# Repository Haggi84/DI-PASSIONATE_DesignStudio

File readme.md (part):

# Package Studio — chip packaging assemblies in FreeCAD, ready to simulate

Build an assembly — chips from GDSII, housings, lids, boards, as many of
each as the design has (a mixed-signal module with an RF chip and a
digital chip, two packages on one board) — wire it, define its ports and
materials, and get a **ready-to-run EM simulation package** for openEMS,
EMerge or Palace, written by OTTER. An assistant on a local model (Ollama)
explains the setup and changes it in plain words.

One toolbar, in the order the work goes:

| Button | What it does |
|---|---|
| **Technology** | Choose the PDK chips are imported with: IHP SG13G2, SkyWater SKY130, or your own folder |
| **Import GDS chips** | One or several layouts at once. Each comes in beside the others, with every drawn layer at its stackup height, its die body, oxide, passivation, bond pads and the PDK's materials. A layout that belongs to another technology is caught |
| **Housing library** | MirrorSemi open-cavity packages, JEDEC outlines, or your own STEP files. Each housing is its own package; its bond fingers become pads; a chip can go straight onto its paddle; a lid can be added |
| **Element Forge** | New housings from a sentence or a pasted datasheet table — a local model (Ollama) fills in the numbers, you check and edit them (values it assumed are marked), live 3-D preview, saved to your own library. Select a housing to change it in place: its pads keep their pin numbers, wires stay on their pins |
| **Import STEP part** | A board (a KiCad board exported as STEP, say), a lid, or a housing as it is |
| **Place** | A chip onto a die paddle or any face (a cavity floor, a board's copper), a lid onto a housing, a package onto a board's footprint — centred. What is placed then *belongs to* what it stands on and moves with it |
| **Move** | Move placed chips, lids, packages or boards — one or several at once — by typed offsets, arrow steps or dragging in the view. Offsets stay editable; wires follow |
| **Pads** | Chip pads from the layout; package pads from the bond fingers (one click finds them all); contact points on any flat surface |
| **Ports** | Simulation ports: rectangles in a face's plane, or standing on an edge up or down to the next edge |
| **Bond wires** | Material, diameter, wedge–wedge or ball–stitch; every bond dimension next to its MIL-STD-883 range; symmetric pairing, chip by chip; rule check |
| **Materials** | What every element is made of — thermal and electrical. The same values go into the EM simulation |
| **EM simulation** | Readiness check, exact chip metal, OTTER's checks, and the package — in one go with *Make simulation package* |
| **EM assistant** | Ask about the setup and have it changed: Ollama on this computer, or Claude / Gemini with your own key |

The menu also has **Layers** (show or hide every layer and part) and
**Export geometry** (STEP, OBJ, MSH for thermal or mechanical work).

## Installing

The workbench is a folder in FreeCAD's user Mod directory:

```
%APPDATA%\FreeCAD\v1-1\Mod\PackageStudio
```

Restart FreeCAD and choose **Package Studio** in the workbench selector. It
needs FreeCAD 1.0 or newer and `gdstk` in FreeCAD's Python
(`"C:\Program Files\FreeCAD 1.1\bin\python.exe" -m pip install gdstk`).
OTTER ships with it (`thirdparty/otter`); the solvers themselves (openEMS,
EMerge, Palace) run where you run the package. For the assistant, install
[Ollama](https://ollama.com) and pull a model (`ollama pull qwen3:8b`).

**For large chips, switch on OpenGL vertex buffers**: Edit › Preferences ›
Display › 3D View › *Use OpenGL VBO*. Turning a 2.3-million-triangle chip then
takes 37 ms a frame instead of 505 ms.

It can be installed beside Package Designer and DI-PASSIONATE: its code is
all in the package `pkgstudio`, its commands are `PS_…`, its settings under
`Mod/PackageStudio`.

## An assembly, step by step

A mixed-signal example: an RF chip and a digital chip, each in its own QFN,
both on one board.

1. **Technology** — pick the PDK. It is remembered.
2. **Import GDS chips** — select both GDS files at once. They come in side
   by side, 0.5 mm apart; each is checked against the technology on its own.
3. **Housing library** — pick a QFN, tick *Put the chip on the die paddle*.
   It takes the first chip not in a housing yet. Do it again for the second:
   the second housing is a second package, set 2 mm beside the first.
4. **Bond wires** — *Pair all, symmetric* pairs each chip with the leads of
   its own package, round its own centre; *Build wires*.
5. **Import STEP part › Board**, then **Place › Package onto a board** for
   each package: select the footprint's pads. The package becomes part of
   the board.
6. **Move** — nudge a package or a chip into its final place; the offsets
   stay editable.
7. **Ports** — draw the ports where the signals go in.
8. **Materials** — check what everything is made of.
9. **EM simulation › Make simulation package** — or fix what its list says
   first.

**Open and look:** `examples/lna_board/lna_rf_em.FCStd` is a finished EM
model — the IHP ALL_LNA in a QFN-24 on its RO4350B board, ports, materials
and EM settings set. Open it after cloning; the EM panel shows how it is
set up. See `examples/lna_board/README.md`.

The same steps as a script, ready to simulate: `examples/lna_qfn40_on_board.py`
(the SG13G2 LNA in a QFN-40 on its RO4350B test board, see `examples/README.md`).

## Element Forge: new housings in seconds

The model never writes geometry: it fills in a fixed set of numbers
(`core/elements.py`, the datasheet symbols D, E, A, e, b, L, D2, E2, A1 and
the lead counts), constrained to that schema by Ollama's structured output.
Every spec — typed, generated or loaded — goes through the same checks:
leads that would overlap, leads too wide for their pitch, too many leads for
the body, no lead length left, a name that disagrees with the numbers. A
spec that fails is handed back to the model once or twice with the exact
numbers; whatever is still wrong is listed with a fix to apply. Then the real
build is analysed like any housing: every lead must be bondable, the paddle
open.

- **Generate**: `QFN-24 4x4 mm, 0.5 mm pitch, exposed pad 2.6 mm`, or a
  datasheet's dimension table pasted in. The fields fill in as the model
  writes them.
- **Change**: `pitch 0.4, two more leads per side` — the element in the form
  is changed, the rest kept.
- Values the model **assumed** are amber (≈) until you change or confirm
  them.
- **Save to library** writes `<FreeCAD user data>/PackageStudio/elements/<name>.json`
  (or `$PKGSTUDIO_ELEMENTS`) — plain JSON, diff- and git-friendly. The
  Housing library lists them under *Mine*.
- Every housing built from numbers (JEDEC or Forge) keeps them
  (`ElementSpec`). **Update housing** rebuilds it in place.

## The design flow: pin list, LVS, assembly house, KiCad, circuit, measurement

The third toolbar, **Design flow**, connects the package to the people
around it (plan and rationale: `docs/plan/`):

| Command | For whom | What it does |
|---|---|---|
| **Pin list & LVS** | chip designer | Reads what the designer intends — CSV (`die,pad,net,kind,lead`), the xschem top cell (`.sch`), the digital flow's LEF — lays the wires **by net** (fixed leads kept as anchors, the rest crossing-free; for 2–3 dies an exact search over the lead arcs) and checks the package against it: opens, shorts, wrong leads, supplies without a lead, bonded `nc` pads, RF leads without ground neighbours |
| **Bonding diagram** | assembly house | SVG/PDF to scale and the wire list (CSV: first bond in µm from the die centre, second bond from the package centre, material, diameter, loop height, length) |
| **KiCad board** | board designer | Reads a `.kicad_pcb` (KiCad 6–9): its stack-up, lines, vias, planes, copper polygons, footprints — the whole board or a region for the EM model; packages go onto its footprints' lands |
| **KiCad library** | board designer | The package as a KiCad footprint (lands numbered as the leads — same numbering and positions as KiCad's own QFN library), a symbol whose pins carry the LVS nets, and a STEP model with dies and wires |
| **Circuit model** | chip designer | Touchstone → passive SPICE subcircuit (vector fitting, scikit-rf) + xschem symbol; with ngspice on the PATH it is simulated and compared with the Touchstone file |
| **Compare with measurement** | everyone who must trust the result | IEEE P370 quality of the measured data, 2x-thru de-embedding, max/RMS Δ per S-parameter, plot and report (`tools/ps_validate.py` does the same from the shell) |

Optional Python packages for the flow: `scikit-rf` (circuit model,
validation), `matplotlib` (plots); `ngspice` on the PATH for the circuit
model's check.

## Multi-chip modules, boards, systems

The second toolbar, **MCM & System**, takes an assembly beyond one die in one
package:

| Command | What it does |
|---|---|
| **Arrange dies (MCM)** | Several dies on one paddle — in a row, a column or corner to corner, a gap apart — and checked: on the paddle (with a margin for the die-attach fillet), clear of each other (≥ 0.15 mm), clear of the bond fingers (`core/mcm.py`) |
| **Wire the MCM** | Bond wires for all dies at once, crossing-free: the leads are shared out among the dies (a weighted Voronoi split of the lead ring), then each die is paired round its own centre. Die-to-die wires are ordinary wires between two chip pads; MIL-STD-883 judges their second bond as on a die pad (3.2.1.4a) |
| **PC/104 board** | A generated CubeSat board, 90.17 × 95.89 × 1.6 mm, 0.254 mm RO4350B over a ground plane on FR-4, corner holes, CubeSat Kit bus headers. From a script, `core/pcb.py` draws QFN land patterns, GCPW with via fences, traces, connectors and component bodies |
| **CubeSat 1U** | Rails, frames, M3 rods, spacers, solar panels, an S-band patch (`core/cubesat.py`) |
| **Into the system** | A board into the stack, at 15 mm pitch or a height you type; the spacers follow |
| **Integration check** | Envelope (100 × 100 × 113.5 mm, ≤ 6.5 mm out of a face, never on a rail), collisions between modules, every board's parts against the room in the stack, mass (≤ 2.00 kg) and centre of gravity (±2 cm) — CubeSat Design Specification Rev 14.1. Masses from the materials' densities |

The reference case is `examples/cubesat_sband_mcm.py`: an S-band receiver
front end from two real SG13G2 dies (the LNA and IHP's open
`i2c-gpio-expander`) in one QFN-32, on a CubeSat COM board, in a 1U CubeSat —
plus the RF path cut out of the board as an openEMS model. See
`examples/README.md`.

## Assemblies: what belongs to what

```
Assembly (the document)
  Board (App::Part)            imported STEP
    Package (App::Part)        placed on the board's footprint
      Housing, Lid             from the library, or STEP
      Chip (App::Part)         placed on the paddle
      Die attach, Bond wires
    Chip                       placed on the board's copper: chip-on-board
  Package 2 …
  Chip                         imported, not placed yet ("loose")
```

Chips come in **loose**, at the document's top level, beside one another.
**Place** puts a chip into the package of the housing it is placed on, or
into the board; a package placed on a board's footprint goes into the
board. From then on it moves with what it stands on, and its place is
kept exactly: only the container changes. A housing is always a package of
its own — a new one goes into the first package without a housing, else
into a new package beside the others.

**Bond wires** belong to the package or board both their pads are in, and
move with it. *Pair all, symmetric* pairs each chip on its own, with the
leads of its own package (or board), so two chips never take each other's
leads.

## Place and Move

**Place** is exact: the object's bottom centre onto the centre of the
selected face (or of several faces, such as a footprint's pads), its +Z
along their normal, turned in quarter steps. *Chip onto a die paddle* needs
nothing selected.

**Move** then moves it from there, *parametrically*: the place Place put it
is kept as its base, and a move is an offset from that base, kept in the
object's *Position* properties:

| Property | Meaning |
|---|---|
| OffsetX, OffsetY | moved along the surface it stands on, mm |
| OffsetAngle | turned about the surface normal, through its own bottom centre |

The X and Y of a move are its container's X and Y laid into the surface —
on a level paddle or board, the package's or board's X and Y, whichever way
the chip itself was turned — so several chips moved together all go the
same way. A turn is about each object's own centre.

In the **Move** panel:

- **select the rows** to move (Ctrl / Shift for several), or select them in
  the view and press *Take 3-D selection* — any face of a chip selects the
  chip;
- **step** them with the arrows (*Step*, default 0.05 mm) and turn them by
  the *Turn step*;
- **type** an offset in the table, or *Move by* ΔX ΔY;
- **drag**: *Drag in the view…*, click to grab, move — everything selected
  follows over its surface, snapped to the step — and click to drop. Esc
  puts everything back. Before grabbing, the arrow keys step and R turns;
- *Back to where placed* sets the offsets to zero; *Keep here as placed*
  makes the current place the new base.

Offsets typed in the property editor move the object too. Moved by other
means (FreeCAD's Transform), the next offset keeps that move. Wires are
rebuilt after every move — during a drag they are hidden and rebuilt on
the drop. Chips that overlap are reported.

## Technologies and the stack

A technology is a folder in `technologies/`: the PDK's KLayout layer
properties (`.lyp` — names and colours), its stackup (`.xml`) and a
`tech.json`. **Every height comes from the stackup XML** — the `.lyp` has
none, and a `.map` file (GDS ↔ LEF/DEF names) neither. Both stackup formats
in use are read and give the same heights:

- schema 2.0 (the bundled files): absolute `Zmin`/`Zmax` per layer and a
  `Substrate Offset`;
- schema 3.0 / 3.1 (IHP's current files, e.g. `SG13G2_FEM_200um.xml` from
  gds2palace): a layer or dielectric placed on another's `Top`/`Bottom`
  edge (`Reference`/`ReferenceEdge`), and `<Variables>` with `=expression`
  values (arithmetic only; nothing else is evaluated).

z = 0 is the top of the silicon. Checked against the PDKs (µm):

| SG13G2 | z | SKY130 | z |
|---|---|---|---|
| Metal1 | 1.04 – 1.46 | li1 | 0.9361 – 1.0361 |
| Metal5 | 5.09 – 5.58 | met1 | 1.3761 – 1.7361 |
| MIM | 5.6043 – 5.754 | met3 | 2.7861 – 3.6311 |
| TopMetal1 | 6.4303 – 8.4303 | met5 | 5.3711 – 6.6311 |
| TopMetal2 | 11.2303 – 14.2303 | | |
| SiO2 / passivation | 0 – 15.7303 / – 16.1303 | SiO2 | 0 – 6.6311 |
| EPI / substrate | −3.75 – 0 / 180 µm | EPI / substrate | −2 – 0 / 298 µm |

On import the chip gets, besides its drawn layers and its silicon:

- **the oxide and passivation**, die-sized, hidden and not pickable (shown,
  they would cover every pad) — offered in the export, not ticked, since
  they enclose the metal;
- **the unused PDK levels** — stack levels the PDK has and this layout does
  not draw (a digital chip without MIM, say), as faint die-sized slabs at
  their true height, listed in **Layers** under *Unused PDK levels*. They
  are not metal and are not ticked in the export.

**The wrong technology** builds nothing: no layer matches, and the chip
comes in as a bare block (an IHP layout imported as SKY130 does exactly
that). Import GDS counts how many of the layout's layers each technology
knows and offers the one that fits — ALL_LNA: SG13G2 knows 68 of 70, SKY130
one marker layer.

## Housings

| Source | What it is |
|---|---|
| **MirrorSemi** | MirrorSemi's pre-moulded open-cavity QFN/DFN packages (mirrorsemi.com), ready for die attach and wire bonding. *Load catalogue* reads their CAD page; a model is downloaded only when chosen, into a cache in your FreeCAD user folder. Nothing of theirs is shipped — their files are "all rights reserved", for your own use. A link that leads nowhere is reported, not imported. |
| **JEDEC** | Open-cavity packages generated from JEDEC outlines: QFN (MO-220), DFN (MO-229), LQFP/TQFP (MS-026), SOIC (MS-012), TSSOP (MO-153). Leadframe (paddle and leads, gull-wing outside where the outline has them) and a body with a cavity down to the bond fingers. |
| **Local folder** | Any folder of your own housing STEP files. |

Every housing, whatever its source, is read the same way: the solid with the
largest footprint is the body; the leadframe piece under its centre is the
die paddle; pieces reaching one side of the body are leads, pieces reaching
two are tie bars. A lead's *bond finger* is its top face where the body does
not cover it. This needs the leadframe as separate solids, as MirrorSemi's
models and the generated packages have it; a fully moulded body exposes no
fingers. Body and leadframe get mould compound and copper alloy C194; change
either in **Materials** (MirrorSemi bodies are pre-moulded — LCP is in the
library).

Lids are generated flat, the size of the body, in glass, ceramic, LCP or Kovar.

## Bond wires

Two bond types, shaped as a bonder makes them:

- **Wedge–wedge** (ultrasonic, aluminium — the default): a wedge on the chip
  pad and one on the lead; the wire leaves the first wedge's heel at the
  tool's wire-feed angle (45° by default), not vertically, and a short tail
  is left beyond the last wedge.
- **Ball–stitch** (thermosonic, gold, copper, silver): a flattened ball with
  the capillary's chamfer cone on the chip pad, the wire leaving it
  vertically, and a crescent stitch on the lead.

**The wire is one swept solid, wedges included.** Its centreline runs over
the first foot, bends out of the heel (radius 1.5 d), follows the loop,
bends into the second foot and runs on into the tail. The cross-section
along it is the round wire in the loop and the flattened bond on each foot,
changing over the bends, as the tool squashes the wire. There are no
separate bond blocks for the wire to sit on. A bond's thickness is not set
but follows from the wire: the flattened section keeps the wire's area
(1.5 d wide → 0.57 d thick). Each foot is sunk a tenth of its thickness into
its pad and cut flat, so **it meets the surface in a flat contact face lying
in the pad's plane** (31.8 × 70 µm for a 25 µm wire's first wedge). This
holds on a tilted surface too: each end follows its own pad's normal. The
loop's highest point is exactly the loop height.

### Wires onto a board: contact points

A board, substrate or any flat face without pads of its own gets
**contact points**: Pads › *Contact points*.

1. Select the face the wires land on and press **Use selected face**. The
   panel shows its size, e.g. *100.0000 x 50.0000 mm (X x Y)*.
2. Choose the **origin**: the *face corner* (default; X runs along the
   face's edge nearest the chip's x axis, Y across it, so a 100 x 50 mm
   face runs from (0, 0) to (100, 50)), or the *chip centre* (X, Y along the
   chip's axes).
3. A **grid with rulers** is drawn on the face in these coordinates:
   labelled lines about ten across the face in 1-2-5 steps (10 mm on a
   100 mm face), fine lines a fifth of that, millimetre labels along the X
   and Y edges. Set the spacing yourself in *Grid*, or switch it off. It is
   temporary: not exported, gone when the panel closes.
4. Type **X** and **Y** in mm and press **Add point**: X 25.5, Y 10 puts it
   exactly there. Or **Click points…** on the face (Esc ends): a red
   crosshair follows the mouse and the panel shows the X and Y a click
   would give, snapped to the fine grid lines (switch off *clicks snap*
   for free positions); a click off the face is refused.
5. The table lists every point's X and Y; edit a value to move the point.
   A point is the size of the bond that lands on it (62.5 x 37.5 µm for
   25 µm wire); *Point size › Apply* resizes the selected ones (or all).
6. Select points in the table and **Mirror** them over X (through the
   face's middle: Y → 50 − Y on a 100 x 50 face), over Y (X → 100 − X), or
   both. With the chip-centre origin the mirror lines are the chip's axes.
   An image already there, or off the face, is not made.
7. **Bond wires › Pair all, symmetric** (or *Pair selected pads*) and
   **Build wires**: their second wedges lie flat on the face.

### The rule check

The rule check applies MIL-STD-883, Test Method 2010 (internal visual),
class level B (Condition B, the default) or S (Condition A):

| Clause | Criterion |
|---|---|
| 3.2.1.1a | Ball diameter 2.0 – 5.0 × wire diameter |
| 3.2.1.1c | Ball: wire centre exit within the pad opening |
| 3.2.1.2a/b | Wedge 1.2 – 3.0 × wide (ultrasonic) or 1.5 – 3.0 × (thermosonic stitch), 1.5 – 6.0 × long |
| 3.2.1.4a | ≥ 75 % (S) / ≥ 50 % (B) of the bond on the die within the pad opening |
| 3.2.1.4d | Tail ≤ 2 wire diameters |
| 3.2.1.4e | Bond completely on the lead |
| 3.2.1.4f | Bond to bond: ≥ 0.25 mil (S) / a gap (B) |
| 3.2.2a | Wire to other wires, bonds, leads, the die edge, the lid: ≥ 2 d (S) / ≥ 1 d (B); class S accepts 1 mil within 5 mil of the bond on the die |
| 3.2.2d | No straight run without an arc |
| 3.2.2e | No wires crossing seen from above, except at different heights with ≥ 2 d |

Two assembly guidelines are reported as notes, not rejects: wire length
≤ 200 × diameter (5 mm for 25 µm) and a loop of at least 75 µm for ball
bonds (neck damage below that) or 2 × diameter for wedges. Each row of the
table shows ✓ or ✗; hovering lists every finding with its clause.

## Ports

**Ports** has its own command. A port is a flat rectangle where the
simulation feeds and measures the model.

**In a face's plane**: select a face (or an edge — the flat face beside it
that stands most upright is taken: a board's top-rim edge gives its edge
face), press **Use selected face**, choose the origin, and type the port's
centre and **Add port**, or **Click port centres…** with the grid and
crosshair. Give its size (W along the face's X, H along its Y), type
(*lumped* or *wave*), impedance (50 Ω) and, for a lumped port, the direction
of its field (±X or ±Y in its own plane). The table edits position, size,
type and impedance; **Mirror selected** mirrors over X, Y or both. Ports are
named Port1, Port2, … (P1 is often a chip pad's name).

**Or draw it on an edge.** **Draw on an edge…**, in the same box, needs no
face chosen first. It takes three clicks per port:

1. Click an edge of a chip layer, a board, a housing or a lid. The port
   starts there.
2. Click again along that edge to set the port's length.
3. Move the mouse up or down and click to set its height.

The port stands upright on the edge, and the next port can be drawn
straight away. **Esc** abandons the port being drawn; **Esc** again ends.
On a chip layer the edge is the side of the drawn GDS polygon nearest the
click, at the layer's top or bottom. The layer is shown as a mesh, and the
mesh's triangle edges are not the polygon's. Two choices set the numbers:

| Choice | Effect |
|---|---|
| **Length: from the two clicks** | The length is between the two clicks. |
| **Length: W above** | The length is W; the second click only says which way along the edge the port runs. |
| **Height: follow the mouse** | The height is where the cursor is. |
| **Height: H above** | The height is H; moving up or down picks the direction. |
| **Height: to the next edge above / below** | The port ends at the nearest edge of other shown geometry over or under its length. That is usually the ground under a trace, or for a chip layer the silicon's top. Moving up or down picks which. |

"Next edge" is measured exactly. B-rep parts (board, housing, lid, die body)
are cut with the port's own plane. A chip's layers are taken from their
GDS polygons: every polygon the port's footprint crosses gives its layer's
bottom and top. The body the port starts on doesn't count: from a trace's
top, the next edge below is the ground, not the trace's own underside.
Hidden layers and the faint slabs of levels the layout does not draw don't
count either. Show the oxide, and its boundaries count too. Type, Z0 and
field direction come from the box above. A port drawn on an edge is an
ordinary port afterwards: in the table, in the exports, and in
`ports.json`.

Ports are drawn as opaque faces, in front of the faces they lie in. A port
on an edge shares its plane with the side faces there, and when it was
drawn see-through the edges behind showed through, so it looked like an
outline.

Ports are drawn as opaque faces, in front of the faces they lie in.

**A lumped port spans the gap between two conductors**, the signal and its
ground: from a trace down to the ground plane, or in a QFN's leadframe
plane from a lead's inner end across to the die paddle. One that touches a
single conductor is warned about; one that touches none is an error — it
would feed nothing.

## Materials

Every element has a material with density, thermal conductivity, specific
heat, CTE, electrical conductivity, permittivity, permeability and loss
tangent. **There is one material system**: what the Materials panel says is
what the exports write and what the EM solver gets; a material changed in
the EM panel is written back to the element. They come from three places:

- **The chip's technology** — every material in the PDK stackup, with the
  PDK's own conductivity and permittivity (SG13G2 Metal1: 21.64 MS/m), and the
  thermal values of the bulk material it is made of.
- **The library** — bond-wire metals, leadframe alloys, moulding compounds,
  laminates, ceramics, glass; typical values with their sources.
- **Your own** — *New material…* in the Materials panel, kept in
  `PackageStudio/materials.json` in FreeCAD's user folder.

From 10⁴ S/m up a material is a conductor in the EM model (Ag-filled die
attach at 10⁵ S/m is one); below, a dielectric with its ε_r and tan δ (doped
silicon at 2 S/m is a lossy one). Set *not simulated* to leave an element
out.

## EM simulation

**EM simulation** opens a panel that goes from the assembly to a
ready-to-run package. **Make simulation package** does it all and stops at
the first thing that would make the result wrong, saying which command
fixes it. The steps, one by one:

**0. Ready to simulate?** — what the assembly still lacks, worst first:

| Error (stops) | Warning (a guess the result depends on) |
|---|---|
| no port, no excited port, two ports with one number | parts without a material — OTTER guesses from name and colour |
| a material not in the library, or without ε_r and σ | a chip not placed in a housing or on a board |
| a chip region too big to mesh | a port touching only one conductor |
| chips overlapping | MIL-STD-883 rejects on the wires |
| a wire that lost a pad; after the build: a port touching no conductor | |

**1. Chip metal** — a whole chip cannot be meshed for EM (ALL_LNA has
600,000 vias) and does not need to be: what the package adds is pad, wire
and lead. So each chip's metal is rebuilt **exactly from its GDS polygons**
inside a region — by default round the pads that have wires, 20 µm beyond
them — for the levels chosen (by default the two highest metals and the vias
between). **Fill is left out**; via arrays become blocks whose conductivity
is scaled by how much of them is via. The rest of the die is its silicon,
oxide and passivation. The table shows how many polygons each chip builds
(at most 60,000).

**2. Model** — a separate document, *<assembly> (EM model)*: every physical
part where it really is (housing, leadframe, die attach, lid, board, wires,
die body, oxide), the chip metal, one face per port, and an air box a
quarter wavelength round everything at the highest frequency (2.6 mm at
30 GHz). The assembly itself is not changed.

**3. Solver** — openEMS (FDTD), EMerge (FEM) or Palace (FEM); frequency
range; mesh density and smallest cell.

**4. Layers and materials** — the layer stack OTTER sees, each layer's
material and where it came from; guessed ones are marked. *Save chosen
materials to the assembly* writes a choice back to the elements.

**5. Ports** — every port as a lumped port with its impedance and its
excitation axis; which one is excited.

**6. Checks** — OTTER's own checks, and the openEMS mesh estimate.

**7. Package** — written by the OTTER add-on itself into a zip: the solver
script and the geometry it loads, the flat model (`.FCStd` + `.ini`, to open
with the OTTER add-on), `overview.svg`, `materials.json` (every layer, its
values and where they came from) and a README with the run command, the
chip regions, the mesh estimate and every remaining finding.

### Click a finding: the fix, shown in the 3-D view

Every line of *0. Ready?* and *6. Checks* can be clicked. A box under the
list explains it in the assembly's terms. The 3-D view zooms to it and
draws:

| Colour | Meaning |
|---|---|
| red | the part the finding is about |
| yellow | the conductors a fix would join |
| green | the fix itself |

Where the fix can be worked out, it is a button; applied, the model is
built and checked again. Otherwise *Open Ports / Materials / Move / Place*
opens the command that fixes it by hand. The preview is temporary: it goes
when another line is clicked, a fix is applied, or the panel closes.

| Finding | What is shown | The fix |
|---|---|---|
| a port with no conductor at one or both ends | the port; the nearest conductor below its centre and above it, in its footprint | the port stretched or shrunk exactly between the two; if only one side has a conductor, that end. With none in its footprint, the nearest conductors anywhere are shown, to move it to |
| a port touching only one conductor | as above | as above |
| wires in cells larger than the wire | the parts named (often via blocks OTTER reads as wires) | their own cells of at most their diameter / 1.5 — fine cells only there |
| too many mesh cells | the part that sets the model's extent | coarse mesh density; smallest cell 2 µm |
| a sub-micron cell | | smallest cell 1 µm |
| no or several excited ports | | excite the first port only |
| air boundary too close | | air box a quarter wavelength away |
| a part without a material, an unplaced or overlapping chip, a broken wire | the parts concerned, selected | *Open Materials / Place / Move / Bond wires* |

## EM assistant

The assistant panel is a chat about the EM setup. It can only do what the
panel can — solver, frequency, material per layer, mesh, ports, checks, and
search OTTER's documentation — through a fixed set of tools, each checked
like a click; it never sees or writes solver code. With every question it
is given the project, where each material came from, and the readiness
findings, so it can say what is missing and which command fixes it.

- **Local model (Ollama)** — the default: free, and nothing leaves the
  computer. The panel says whether Ollama answers at its URL
  (`http://127.0.0.1:11434`) and lists the models pulled.
- **Claude** or **Gemini** with your own API key: the project description
  and your questions go to that provider. A key is kept for the session,
  or in FreeCAD's `user.cfg` if you tick *remember*.

Build the model first (*Build model* or *Make simulation package*).

## Export geometry: what is written, exactly

Chip layers are rebuilt from the GDS polygons at export time — never from
what the view shows. Every polygon becomes a prism of its layer's height,
vertex for vertex. Metal fill is metal and is included; slits are cut out;
pin, label and boundary shapes are markers and are not.

| File | Content |
|---|---|
| STEP | Exact solids, one named product per element (`Chip/Metal1_8_0`, `Wires/Wire P1 - 1`, …) |
| OBJ | Triangle meshes, one named group per element, coloured by material. Chip layers are exact; curved parts follow the chosen deviation |
| MSH | Gmsh 4.1 volume mesh from the exact STEP: one physical group per element, and one per material (`MAT_…`) |
| `…_materials.json/.csv` | Each element, its material and every property, with units — written beside every export |

Exact solids cost about 0.6 ms per layout polygon; the export dialog says how
long before it starts, and can be cancelled.

**Only a section**: tick *Only a section* in the export dialog and press
**Pick in view…**: the view turns to the top; click two opposite corners —
a red rectangle follows the mouse — or type x and y from/to in mm. Only what
lies inside is written, at every height: chip layers are cut polygon by
polygon before any solid is built (so a section of a large chip is quick),
everything else is cut to the box. Elements wholly outside are left out, and
so are ports outside it from `_ports.json`.

## Limits

- Overlapping polygons on one layer are exported as overlapping prisms (only
  layers with slits are merged).
- Elements in an MSH geometry export are meshed independently (not conformal
  across touching elements).
- The EM model's passivation has no openings over the pads; the wire's foot
  takes their place.
- Housing analysis needs the leadframe as separate solids.
- Material values in the library are typical; for a production simulation,
  use your suppliers' datasheets (add them as your own materials).

## Tests

```powershell
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
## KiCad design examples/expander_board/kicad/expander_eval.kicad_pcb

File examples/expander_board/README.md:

# Expander evaluation board — chip, package, board, EM

The IHP i2c-gpio-expander (SG13G2, open MPW TO_Nov2024) from die to a
board that does something, back into FreeCAD, and on to an EM model.

## What the board does

It makes the expander usable from any 3.3 V I2C controller (Raspberry Pi,
microcontroller, Qwiic / STEMMA QT boards; daisy-chained over J1/J2):

| Block | Parts | Why |
|---|---|---|
| Supply | J1/J2 3.3 V → U2 AP2112K-1.2 → R2 0 Ω → U1 VDD (leads 2, 13) | the core takes 1.1–1.2 V; R2 lifted = an ammeter for the core current |
| Decoupling | C4/C5 100 nF at each VDD lead, C6 1 µF, C2/C3 1 µF at the LDO, C1 10 µF | |
| Clock | X1 50 MHz CMOS oscillator (Abracon ASE, 3.3 V) → R1 33 Ω at the source → lead 7 | the design is synchronous at 50 MHz from an external clock (IHP); the one fast net |
| Reset | R6 10 k / C8 100 nF (~1 ms), SW1, J4 | IHP: hold reset ≥ 1 µs while the core supply settles |
| I2C | R3/R4 2.2 kΩ (400 kHz fast mode), R5 10 k on INT | the pads are open drain, pull-ups needed (IHP) |
| Address | R7–R9 10 k pull-downs, JP1–JP3 to 3.3 V | default 0b000 |
| GPIO | J3 2x5 header (GPIO0–7, 3.3 V, GND), D1–D8 with 1 kΩ | |
| Test | TP1 CLK, TP2 +1V2, TP3 +3V3, TP4 GND | |

4 layers, 45 x 32 mm, 1.6 mm FR-4: F.Cu signals over In1 = GND, In2 = 3.3 V
(both layer type "power plane": no tracks on them), B.Cu, ground pours on
both outer layers. Every SMD pad of GND and 3.3 V reaches its plane through
a short track and a via (fan-out in `route_board.py`).

**Open point — read this first.** The die has no IOVDD/IOVSS pads (IHP's
`doc/source/known-issues.rst`): the IO ring has no supply pad of its own.
Whether the IOs work at all, and at which levels, is not known. The board
is built as the chip was meant to be used (3.3 V IO); it is also the test
fixture to find out — TP1–TP4, R2 for the core current, J4 for reset/INT.

The package: IHP packages its open tapeouts in QFN or open QFN with 24 to
64 pins, so a **QFN-24 4x4**, not a QFN-20: 20 wires, 4 leads unused.

## Files

| File | What |
|---|---|
| `expander_pinlist.csv` | the pin list with the board's net names (signal pads by GDS name, supply pads by their GDS labels) |
| `make_package.py` | step 1 (FreeCAD): die in QFN-24, wires by the pin list, LVS, MIL-STD-883, KiCad library, bonding diagram |
| `make_board.py` | step 2 (KiCad's Python): schematic, project, placed board |
| `route_board.py` | step 3 (KiCad's Python + Freerouting): routing, ground pours |
| `check_netlist.py` | the schematic's netlist against the design, ERC-like checks |
| `make_assembly.py` | step 4 (FreeCAD): the board back in, package on U1, the clock path cut out |
| `kicad/` | **the KiCad project** — open `expander_eval.kicad_pro` |
| `doc/` | schematic PDF, board picture, DRC report |

`kicad/` is written by KiCad 7 (schematic, board) and by Package Studio
(`ExpanderEval.*`, KiCad 8 format): open it with **KiCad 8 or 9**, which
converts the KiCad 7 files when you save.

## Checked

- Package: 20 wires, LVS 0 errors, MIL-STD-883 TM 2010 0 rejects, wires 1.42–1.80 mm.
- Schematic: its netlist (kicad-cli) equals the design — 29 nets, 128 pins;
  every power input driven, no two outputs on a net, no single-pin net.
  KiCad's own ERC was not run here (KiCad 7's kicad-cli has none): run it.
- Board: fully routed (0 unconnected); DRC 0 errors, 32 warnings (silkscreen
  overlaps — tidy the reference texts before ordering). KiCad's own ERC and
  DRC run in the KiCad GUI: 0 errors each (the one ERC warning is KiCad 7
  not reading the KiCad 8 library).
- FreeCAD: the board reads back with all 29 nets, the package lands with
  lead 1 on pad 1.

Found on the way and fixed in Package Studio:
- the exported QFN-24 4x4 footprint had touching corner lands (pads 6/7 =
  GPIO5/CLK shorted): `pcb.qfn_lands` keeps 0.2 mm between corner lands;
- KiCad zone fills with holes (one outline with slits) came in with the
  holes misread — the In1 ground under U1 was missing: `kicad_board._rings`;
- the EM panel built the model with OTTER's default 1 µm cells and ran out
  of memory on a board cut-out: it now takes the panel's mesh setting;
- the generated openEMS script's graded-mesh helper took > 7 GB for ~700
  mesh regions: Package Studio evaluates it in chunks (same lines, 0.45 GB).

## Steps

In FreeCAD (Package Studio):

1. *Import GDS* → `examples/data/i2c_gpio_expander_SG13G2Top.gds.gz`.
2. Housing from the JEDEC catalogue: **QFN-24 4x4**; *Place* the chip on the paddle.
3. *Pin list & LVS* → *Load pin list…* → `expander_pinlist.csv` → *Lay wires by net* → *Check (LVS)*.
4. *Bonding diagram* → a folder (for the assembly house).
5. *KiCad library* → a folder: footprint, symbol, STEP. (Already in `kicad/`.)

In KiCad 8/9:

6. Open `kicad/expander_eval.kicad_pro`. The project's library tables
   point at `ExpanderEval.*` in the project folder.
7. Schematic: *Inspect → Electrical Rules Checker*. Change what you need
   (another oscillator, other connectors), then *Tools → Update PCB from
   Schematic*.
8. Board: check, tidy the silkscreen, *Inspect → Design Rules Checker*,
   refill zones (B). Re-route if you moved things (interactive router, or
   Freerouting as in `route_board.py`).
9. Save.

Back in FreeCAD:

10. *KiCad board* → `expander_eval.kicad_pcb`, region empty → the whole
    board. Select the package and U1's lands → *Place*.
11. *KiCad board* again, region **`113, 110, 126.5, 125`** (KiCad mm): the
    clock path X1 → R1 → U1 with the ground around it. Place the package on U1.
12. *Ports* and 13. *EM simulation*: step by step, with screenshots, in the
    guide "Anleitung: Expander-Board in KiCad und Package Studio bis zur
    EM-Simulation" (a Claude doc). In short: four ports — X1's output and
    U1's leads 7 and 8 standing from the land down to In1, R1 as a 33-ohm
    lumped port that is not excited —; chip metal "No metal", 0.01–3 GHz,
    mesh coarse / 50 µm set before the build; *Make simulation package*:
    5.15 M cells, ~0.8 GB. `make_assembly.py` sets the same ports.

Scripted, the same:

    freecadcmd examples/expander_board/make_package.py
    python3   examples/expander_board/make_board.py         # KiCad's Python
    python3   examples/expander_board/route_board.py freerouting.jar
    freecadcmd examples/expander_board/make_assembly.py

`make_board.py` writes the board unrouted: run `route_board.py` after it.

Sources: IHP-GmbH/TO_Nov2024 `i2c-gpio-expander` (pin-out, design notes,
known issues; GPLv3), packaging options in that repository's README.

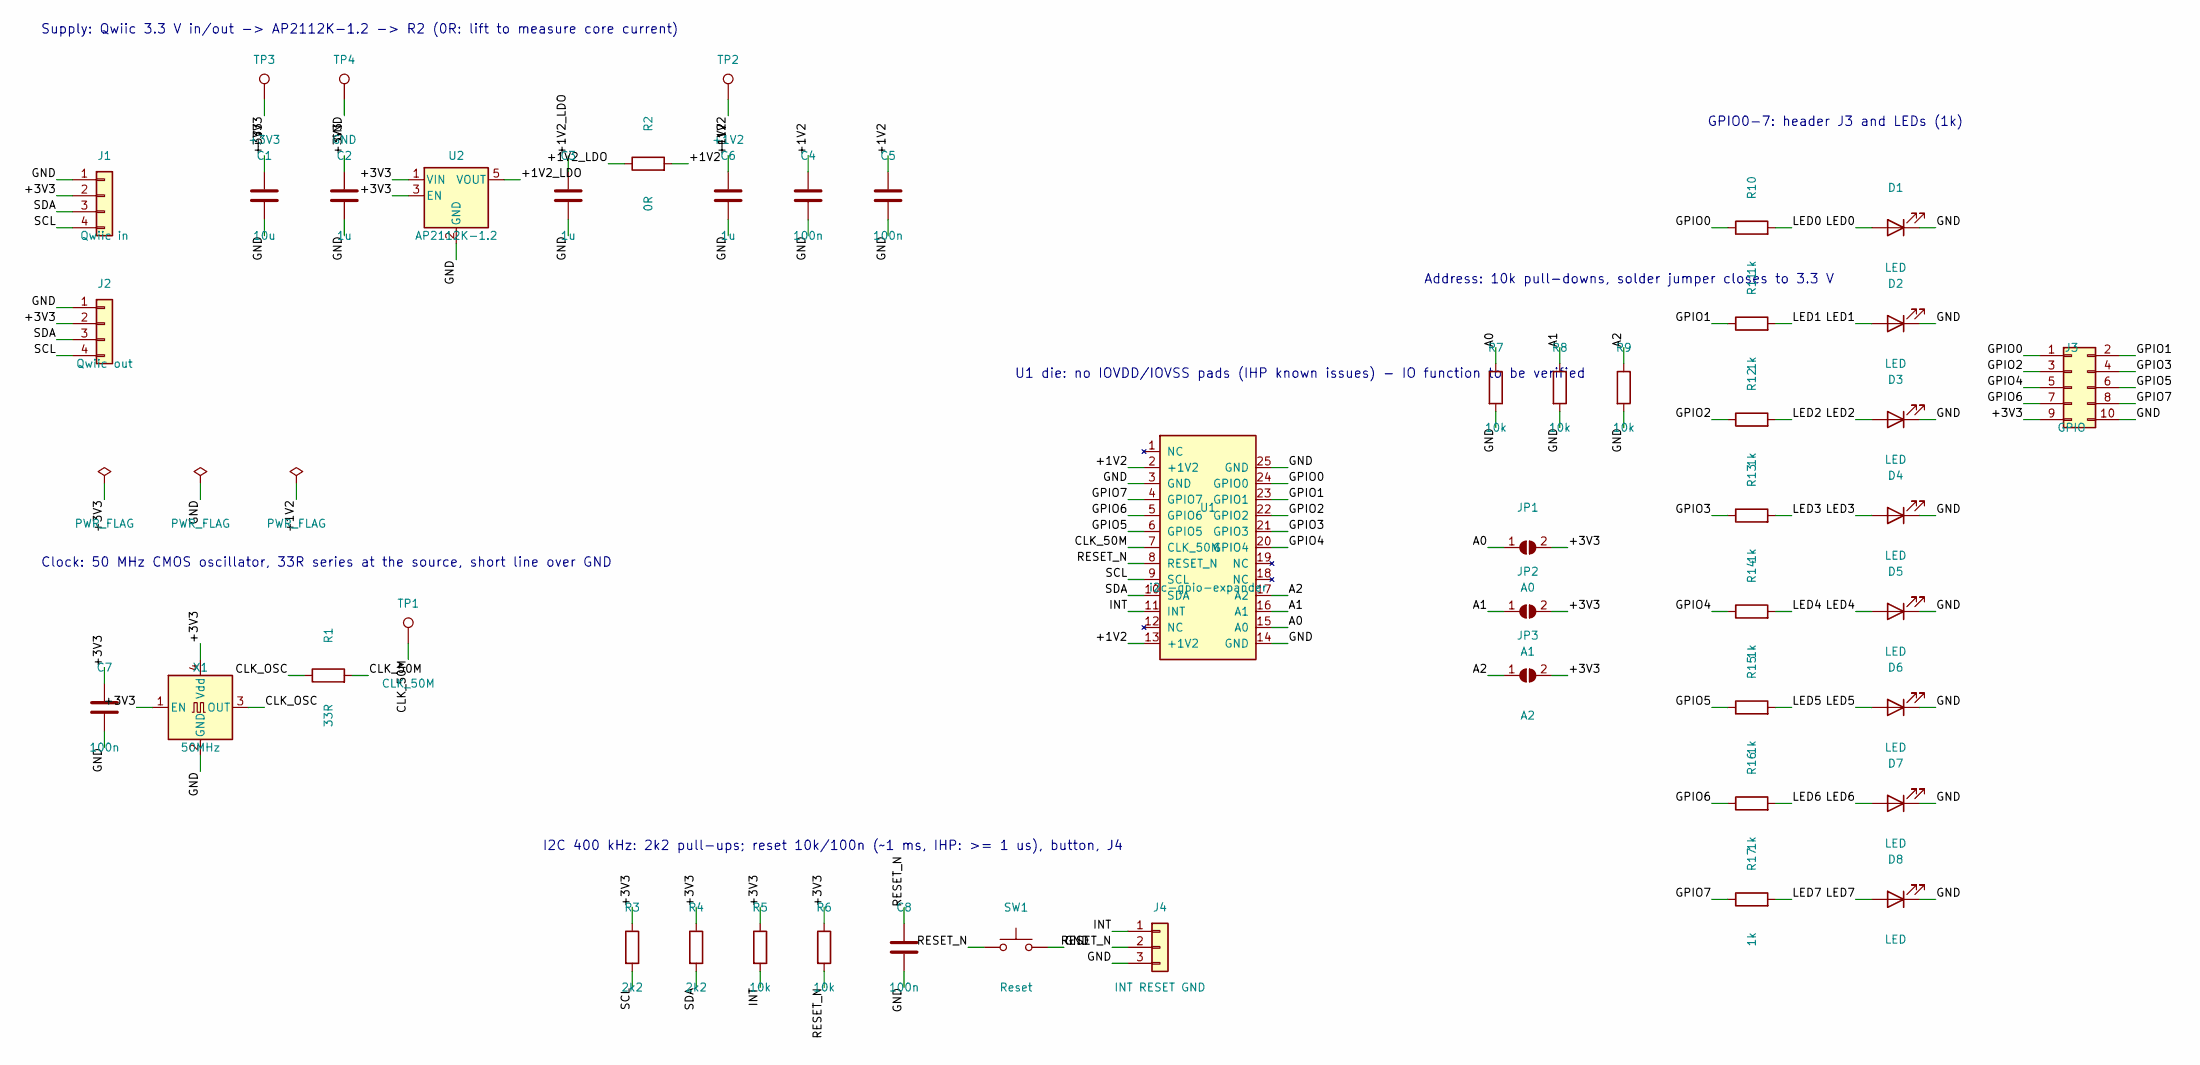
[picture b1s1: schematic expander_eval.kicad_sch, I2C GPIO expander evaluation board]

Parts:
C1: 10u; C_0805_2012Metric
C2, C3, C6: 1u; C_0402_1005Metric
C4, C5, C7, C8: 100n; C_0402_1005Metric
D1, D2, D3, D4, D5, D6, D7, D8: LED; LED_0603_1608Metric
J1: Qwiic in; JST_SH_SM04B-SRSS-TB_1x04-1MP_P1.00mm_Horizontal
J2: Qwiic out; JST_SH_SM04B-SRSS-TB_1x04-1MP_P1.00mm_Horizontal
J3: GPIO; PinHeader_2x05_P2.54mm_Vertical
J4: INT RESET GND; PinHeader_1x03_P2.54mm_Vertical
JP1: A0; SolderJumper-2_P1.3mm_Open_RoundedPad1.0x1.5mm
JP2: A1; SolderJumper-2_P1.3mm_Open_RoundedPad1.0x1.5mm
JP3: A2; SolderJumper-2_P1.3mm_Open_RoundedPad1.0x1.5mm
R1: 33R; R_0402_1005Metric
R2: 0R; R_0402_1005Metric
R3, R4: 2k2; R_0402_1005Metric
R5, R6, R7, R8, R9: 10k; R_0402_1005Metric
R10, R11, R12, R13, R14, R15, R16, R17: 1k; R_0402_1005Metric
SW1: Reset; SW_SPST_TL3342
TP1: CLK_50M; TestPoint_Pad_D1.0mm
TP2: +1V2; TestPoint_Pad_D1.0mm
TP3: +3V3; TestPoint_Pad_D1.0mm
TP4: GND; TestPoint_Pad_D1.0mm
U1: i2c-gpio-expander; QFN-24_4x4_Expander
U2: AP2112K-1.2; SOT-23-5
X1: 50MHz; Oscillator_SMD_Abracon_ASE-4Pin_3.2x2.5mm

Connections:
+1V2: C4.1, C5.1, C6.1, R2.2, TP2.1, U1.2 (+1V2), U1.13 (+1V2)
+1V2_LDO: C3.1, R2.1, U2.5 (VOUT)
+3V3: C1.1, C2.1, C7.1, J1.2, J2.2, J3.9, JP1.2 (B), JP2.2 (B), JP3.2 (B), R3.1, R4.1, R5.1, R6.1, TP3.1, U2.1 (VIN), U2.3 (EN), X1.1 (EN), X1.4 (Vdd)
A0: JP1.1 (A), R7.1, U1.15 (A0)
A1: JP2.1 (A), R8.1, U1.16 (A1)
A2: JP3.1 (A), R9.1, U1.17 (A2)
CLK_50M: R1.2, TP1.1, U1.7 (CLK_50M)
CLK_OSC: R1.1, X1.3 (OUT)
GND: C1.2, C2.2, C3.2, C4.2, C5.2, C6.2, C7.2, C8.2, D1.1 (K), D2.1 (K), D3.1 (K), D4.1 (K), D5.1 (K), D6.1 (K), D7.1 (K), D8.1 (K), J1.1, J2.1, J3.10, J4.3, R7.2, R8.2, R9.2, SW1.2, TP4.1, U1.3 (GND), U1.14 (GND), U1.25 (GND), U2.2 (GND), X1.2 (GND)
GPIO0: J3.1, R10.1, U1.24 (GPIO0)
GPIO1: J3.2, R11.1, U1.23 (GPIO1)
GPIO2: J3.3, R12.1, U1.22 (GPIO2)
GPIO3: J3.4, R13.1, U1.21 (GPIO3)
GPIO4: J3.5, R14.1, U1.20 (GPIO4)
GPIO5: J3.6, R15.1, U1.6 (GPIO5)
GPIO6: J3.7, R16.1, U1.5 (GPIO6)
GPIO7: J3.8, R17.1, U1.4 (GPIO7)
INT: J4.1, R5.2, U1.11 (INT)
LED0: D1.2 (A), R10.2
LED1: D2.2 (A), R11.2
LED2: D3.2 (A), R12.2
LED3: D4.2 (A), R13.2
LED4: D5.2 (A), R14.2
LED5: D6.2 (A), R15.2
LED6: D7.2 (A), R16.2
LED7: D8.2 (A), R17.2
RESET_N: C8.1, J4.2, R6.2, SW1.1, U1.8 (RESET_N)
SCL: J1.4, J2.4, R3.2, U1.9 (SCL)
SDA: J1.3, J2.3, R4.2, U1.10 (SDA)

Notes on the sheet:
Supply: Qwiic 3.3 V in/out -> AP2112K-1.2 -> R2 (0R: lift to measure core current)
Clock: 50 MHz CMOS oscillator, 33R series at the source, short line over GND
I2C 400 kHz: 2k2 pull-ups; reset 10k/100n (~1 ms, IHP: >= 1 us), button, J4
Address: 10k pull-downs, solder jumper closes to 3.3 V
GPIO0-7: header J3 and LEDs (1k)
U1 die: no IOVDD/IOVSS pads (IHP known issues) - IO function to be verified

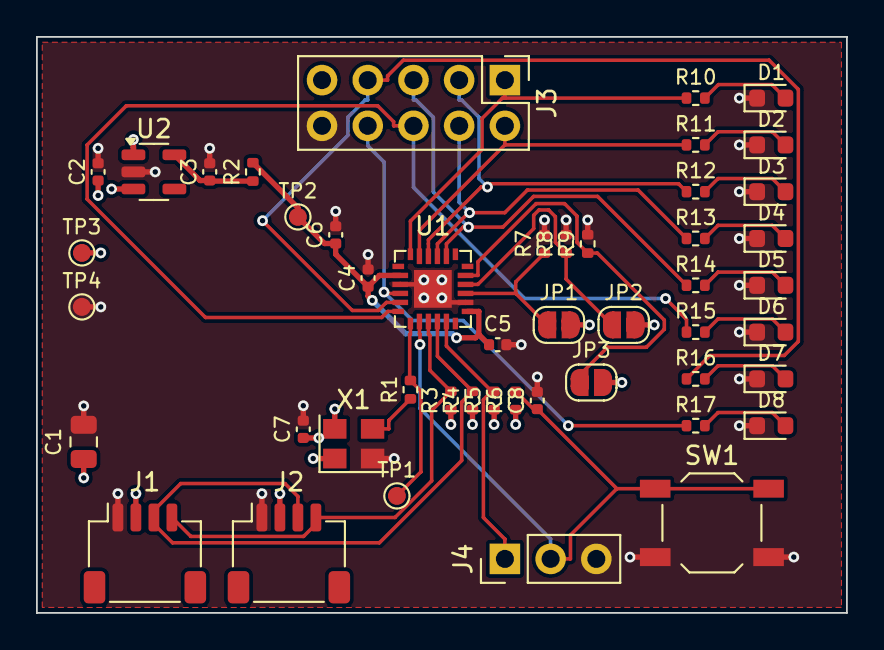
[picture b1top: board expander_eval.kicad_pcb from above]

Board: 4 copper layers, 45.0 x 32.0 mm, 48 parts (0 on the bottom side), 29 nets.

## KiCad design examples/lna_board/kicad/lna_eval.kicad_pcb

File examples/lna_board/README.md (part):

# ALL_LNA evaluation board — package, RF board, EM model

The IHP SG13G2 low-noise amplifier **ALL_LNA** in a **QFN-24 4x4**, on a
two-layer **RO4350B** board laid out for RF, and the RF path cut out as an
**openEMS** model with four ports — from GDS to a ready-to-run simulation
package.

| Board (KiCad, top) | EM model (`lna_rf_em.FCStd`) |
|---|---|
|  |  |

## Quick start: open the finished model

After cloning, open **`examples/lna_board/lna_rf_em.FCStd`** in FreeCAD
(1.1, with Package Studio installed). Everything is set; nothing has to be
generated first.

| Where | What you see |
|---|---|
| Model tree | `LNA eval board (RF path)`: the board cut-out with the package on U1, the six RF die pads, `EM settings` |
| **EM simulation** panel | Solver openEMS, 0.5–6 GHz, mesh *coarse*, smallest cell 50 µm, chip metal *No metal* — read from the document |
| **Ports** panel | P1–P4, 50 Ω each, only P1 excited |
| **Materials** panel | copper, RO4350B (Dk 3.66, tan δ 0.0037), C194 leadframe, mould compound, AlSi1 wires, SG13G2 die stack |
| Property view, `EM settings` | the EM choices with a note why |
| Property view, chip `ALL_LNA` | `EmChipMetal = none`; `GdsPath`, `TechFolder` |

Then, in the EM panel: **Build model** → **Make simulation package**. The
package (~4.1 M cells, 0.7 GB RAM) is written to the folder set under
*7. Package*.

The chip's GDS and technology paths in the file are those of the computer
it was saved on; Package Studio finds `examples/data/ALL_LNA.gds` and
`technologies/IHP-SG13G2` in your clone by itself.

## Files

| File | What it is |
|---|---|
| `lna_rf_em.FCStd` | **the ready EM model** (RF cut-out, package, ports, EM settings), ~24 MB |
| `lna_pinlist.csv` | pin list: die pad → net → lead, ground-signal-ground at the RF pads |
| `kicad/` | KiCad project `lna_eval` (schematic, routed board, stackup, net classes, DRC rules, `LNAEval` library) |
| `make_package.py` | step 1: chip into the QFN-24, wires, LVS, bonding diagram, KiCad library |
| `make_board.py` | step 2: the KiCad project (run with KiCad's Python, `pcbnew`) |
| `make_assembly.py` | step 3: board back into FreeCAD, package on U1, RF cut-out, die pads, ports, EM settings; writes `lna_rf_em.FCStd` |
| `add_em_ports.py` | the ports for a cut-out made by hand in the GUI (FreeCAD Python console) |
| `out/` | generated, not in git (`.gitignore`) |

The chip itself is `examples/data/ALL_LNA.gds` (0.78 × 0.98 mm).

## Rebuild everything

```text
# FreeCAD Python console (View → Panels → Python console), from the repository root
exec(open(r"examples/lna_board/make_package.py").read())      # out/package/
exec(open(r"examples/lna_board/make_assembly.py").read())     # out/assembly/, lna_rf_em.FCStd

# KiCad's Python (only when the board changes)
python3 examples/lna_board/make_board.py                       # kicad/
```

`make_assembly.py` imports step 1 itself; `make_board.py` needs step 1's
`out/package/` (footprint, symbol, STEP). `freecadcmd` works too where it
finds the add-on's modules (`gdstk`); on Windows the GUI console is the
safe way.

The step-by-step guide with screenshots (GUI way, in German):
*Anleitung: LNA-Board in KiCad und Package Studio bis zur EM-Simulation*.

## Design

**Band.** Evaluated in S-band, 2.2–2.3 GHz (CubeSat downlink); board and
simulation to 6 GHz, because stability is decided outside the band too and
wire and lead resonances lie above it. Another band: change the frequency
in the EM panel; the lines are broadband.

**Package, by IHP's criteria.** IHP packages in QFN / open QFN, 24 to 64
pins (0.5 mm pitch), and offers StratEdge encapsulation for RF. The LNA
needs 16 wires; what matters is their length (~1 nH/mm, 1.5 nH is j21 Ω
at 2.3 GHz). So the smallest: QFN-24 4x4 (JEDEC MO-220). RF wires
1.54 / 1.57 mm, all 1.45–1.88 mm, LVS clean, MIL-STD-883 clean.

**Bonding, ground-signal-ground.** GND14–RFIN–GND15 on leads 3–4–5,
GND4–RFOUT–GND3 on 14–15–16: a return wire beside each RF wire (smaller
loop, less inductance, input and output shielded from each other). VTMP
and the calibration structures are not bonded.

**Board.**

| | |
|---|---|
| Material | RO4350B 0.508 mm, 2 layers, 35 µm Cu, ENIG; Dk 3.66 (design), tan δ 0.0037 |
| Layers | top: signals and ground pour; bottom: one unbroken ground (layer type *power*: nothing routed) |
| RF line | grounded coplanar waveguide, 50 Ω: w 0.85 mm, gap 0.20 mm, ε_eff 2.57 |
| Via fences | both sides, 1 mm off the line centre, 1 mm pitch |
| Connectors | edge-launch SMA, Samtec SMA-J-P-X-ST-EM1 (to 20 GHz) |
| DC blocks | 10 pF C0G 0603, 8 mm from the edge |
| Compensation | C3/C4 0402, not fitted, 1.55 mm before each RF land: ~L/Z0² = 0.6 pF makes the wire a 50 Ω low-pass section |
| Bias | from the lab: VCC via ferrite + 10 µF / 1 µF / 10 nF / 100 pF (at the lead); IDC via 100 Ω / 10 nF; heater pins straight to J3 |
| 2x-thru | J4–J5, 35.5 mm = twice SMA-to-land (17.75 mm), same parts: de-embedding with IEEE P370 |
| Checks | DRC 0 errors, 0 unconnected; schematic netlist = board |

## EM model

Cut-out (KiCad mm, y down): `110.5, 108.5, 129.5, 116` — U1, 7.25 mm of
each line (cut between two fence vias, ~14 substrate heights from the
package), fences and 3 mm of ground each side.

| Port | Where | Why |
|---|---|---|
| P1 | input line's cut end, line to bottom ground (0.508 mm) | fed as from the SMA; **excited** |
| P2 | on the die, RFIN to GND14, flat across the 44 µm gap | where the LNA's own S-parameters are defined |
| P3 | on the die, RFOUT to GND3 | as P2, output |
| P4 | output line's cut end | 50 Ω termination |

Die metal is left out (`EmChipMetal = none`): with the full TopMetal2 the
LNA's inductors would hang on P2/P3. Only the six RF pads are in, as
3 µm TopMetal2 blocks. The LNA enters later through its own S-parameters.

Mesh: 50 µm smallest cell in x/y; z is capped at 10 µm (half the copper)
by Package Studio, so the port ends and the 35 µm copper stay on mesh
lines.

## Run and evaluate

```powershell
cd <package>\simulation
$env:SETUP_ONLY="1"; python lna_rf_em_EM_openEMS.py      # build and show the model only
Remove-Item Env:SETUP_ONLY
python lna_rf_em_EM_openEMS.py                            # simulation_output\Sparameters.csv / .png
```

Switches: `OPENEMS_THREADS`, `END_DB=-40`, `MIN_CELL_UM=25` (finer x/y),
`MIN_CELL_Z_UM`.

| Result | Meaning |
|---|---|
| S21 | loss from the line end to the die pad — adds almost 1:1 to the LNA's noise figure |
| S11 | match of the input transition |
| S31, S41 | coupling from input to the die output / output line: the feedback around the LNA, i.e. its stability in the package |

Plausible: S21 a few tenths of a dB below 0 in band; S31/S41 well below.
S21 near −100 dB means a floating port (see below).

Next, in this order: convergence (`MIN_CELL_UM=25`, ~21 M cells, 3.4 GB;
ΔS21 < 0.1 dB in band → the coarse mesh is enough) · the full 4 × 4 matrix
(excite P1…P4 in turn) · cascade with the LNA's 2-port S-parameters
(Circuit model, ngspice or scikit-rf: gain, NF, K/µ) · C3/C4 swept
0.3–1 pF · VNA measurement de-embedded with the 2x-thru (P370).

## Limits of the model

- GND14 and GND15 are joined only through their wires and the board, not
  by the die's ground net; small, since P2 measures RFIN against GND14.
- P1/P4 are line-to-plane ports on a GCPW; the 7.25 mm of line to the land
  are part of the result and can be removed in the circuit model.
- FDTD resolves 3 µm pads and a 20 mm board at once; for the die region
  alone a FEM solver (Palace) is more accurate.

## Troubleshooting

| Symptom | Cause | Fix |
|---|---|---|
| S11 ≈ 0 dB, S21 ≈ −100 dB | port ends lost by a too coarse z mesh | write the package with this version, or `$env:MIN_CELL_Z_UM="10"` |
| LVS: *no die* | chip renamed / imported from a 7-Zip folder name | import `ALL_LNA.gds` directly |
| KiCad: `LNAEval:QFN-24_4x4_LNA` missing | `kicad/` copied without `LNAEval.pretty` | copy the whole folder |
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
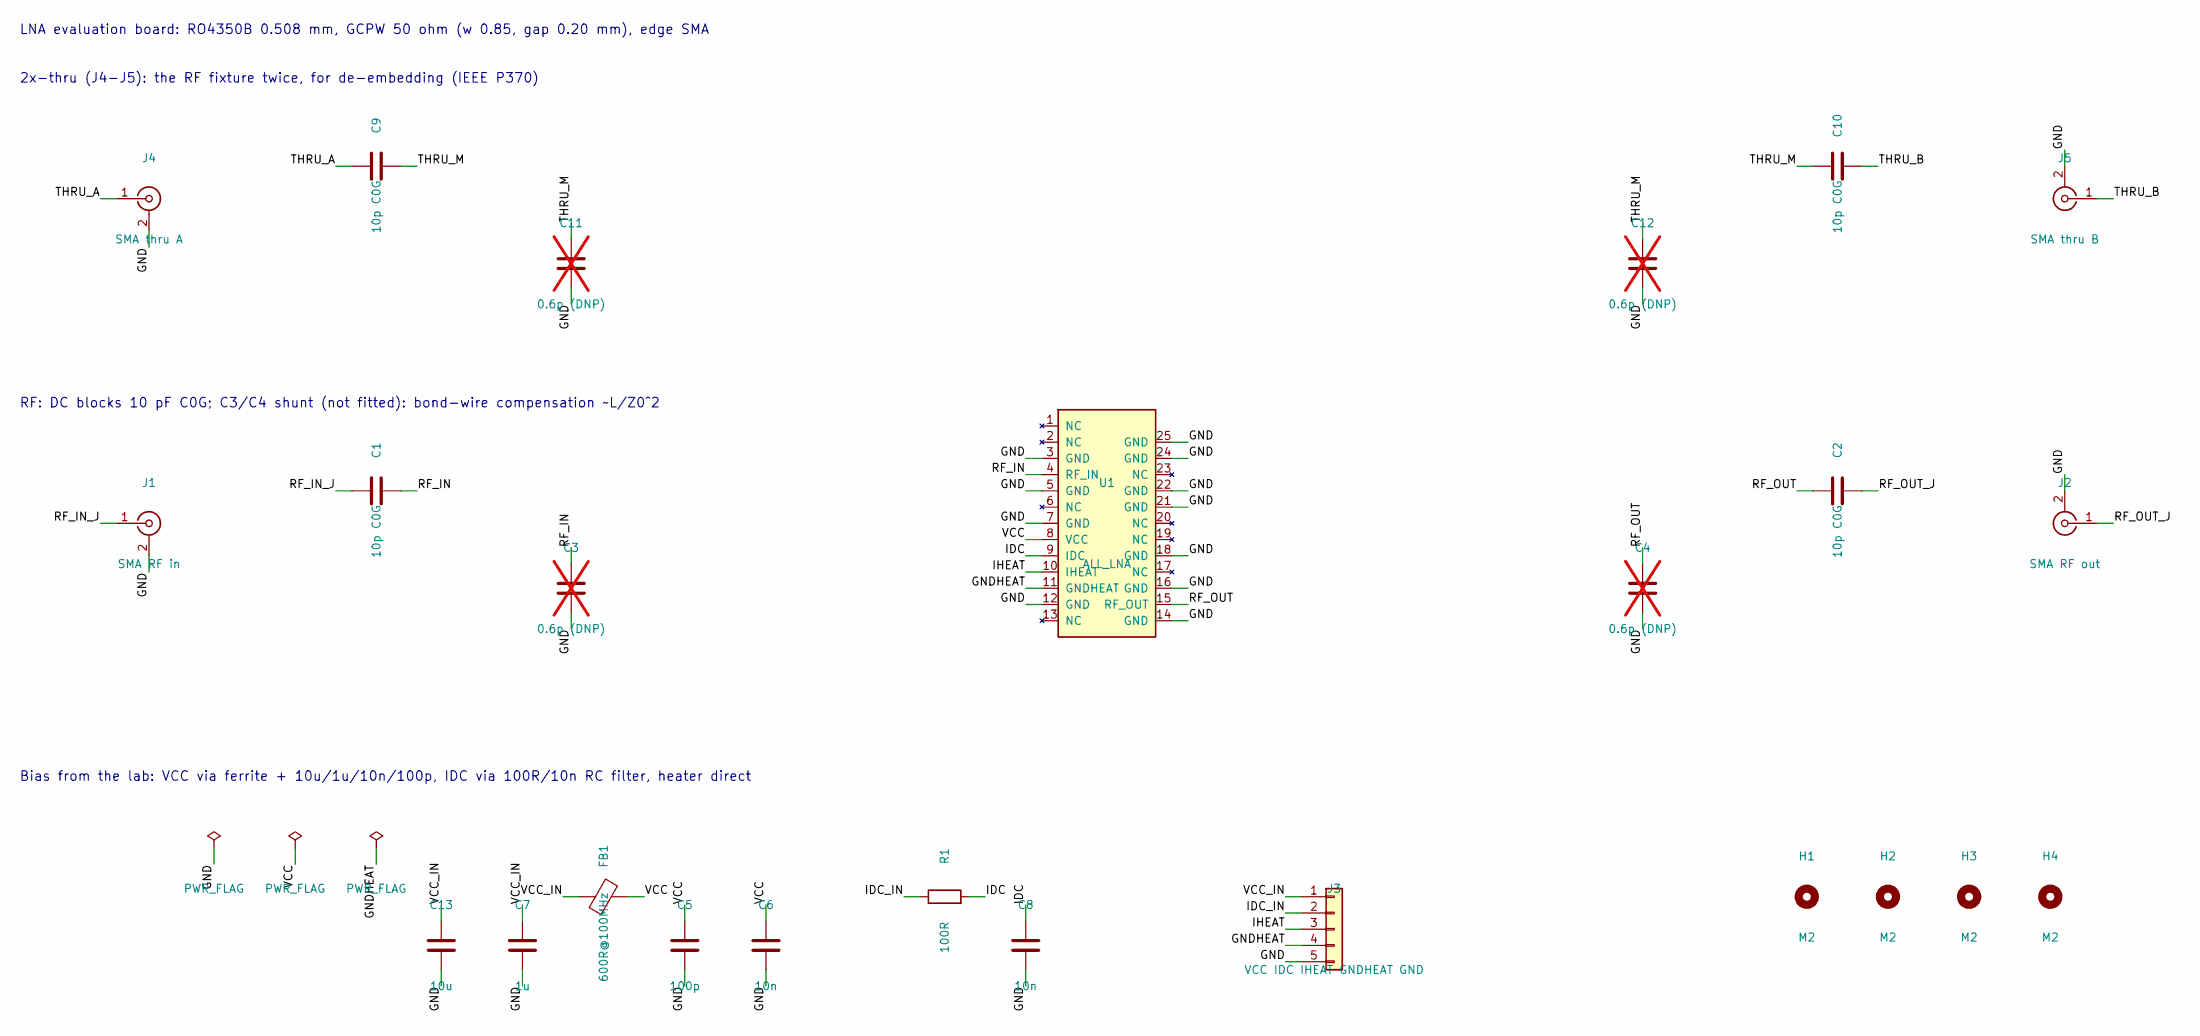
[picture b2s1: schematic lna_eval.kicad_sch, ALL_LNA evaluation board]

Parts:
C1, C2, C9, C10: 10p C0G; C_0603_1608Metric
C3, C4, C11, C12: 0.6p (DNP); C_0402_1005Metric; not fitted
C5: 100p; C_0402_1005Metric
C6, C8: 10n; C_0402_1005Metric
C7: 1u; C_0603_1608Metric
C13: 10u; C_0805_2012Metric
FB1: 600R@100MHz; L_0603_1608Metric
H1, H2, H3, H4: M2; MountingHole_2.2mm_M2
J1: SMA RF in; SMA_Samtec_SMA-J-P-X-ST-EM1_EdgeMount
J2: SMA RF out; SMA_Samtec_SMA-J-P-X-ST-EM1_EdgeMount
J3: VCC IDC IHEAT GNDHEAT GND; PinHeader_1x05_P2.54mm_Vertical
J4: SMA thru A; SMA_Samtec_SMA-J-P-X-ST-EM1_EdgeMount
J5: SMA thru B; SMA_Samtec_SMA-J-P-X-ST-EM1_EdgeMount
R1: 100R; R_0402_1005Metric
U1: ALL_LNA; QFN-24_4x4_LNA

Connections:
GND: C3.2, C4.2, C5.2, C6.2, C7.2, C8.2, C11.2, C12.2, C13.2, J1.2 (Ext), J2.2 (Ext), J3.5, J4.2 (Ext), J5.2 (Ext), U1.3 (GND), U1.5 (GND), U1.7 (GND), U1.12 (GND), U1.14 (GND), U1.16 (GND), U1.18 (GND), U1.21 (GND), U1.22 (GND), U1.24 (GND), U1.25 (GND)
GNDHEAT: J3.4, U1.11 (GNDHEAT)
IDC: C8.1, R1.2, U1.9 (IDC)
IDC_IN: J3.2, R1.1
IHEAT: J3.3, U1.10 (IHEAT)
RF_IN: C1.2, C3.1, U1.4 (RF_IN)
RF_IN_J: C1.1, J1.1 (In)
RF_OUT: C2.1, C4.1, U1.15 (RF_OUT)
RF_OUT_J: C2.2, J2.1 (In)
THRU_A: C9.1, J4.1 (In)
THRU_B: C10.2, J5.1 (In)
THRU_M: C9.2, C10.1, C11.1, C12.1
VCC: C5.1, C6.1, FB1.2, U1.8 (VCC)
VCC_IN: C7.1, C13.1, FB1.1, J3.1

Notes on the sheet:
LNA evaluation board: RO4350B 0.508 mm, GCPW 50 ohm (w 0.85, gap 0.20 mm), edge SMA
2x-thru (J4-J5): the RF fixture twice, for de-embedding (IEEE P370)
RF: DC blocks 10 pF C0G; C3/C4 shunt (not fitted): bond-wire compensation ~L/Z0^2
Bias from the lab: VCC via ferrite + 10u/1u/10n/100p, IDC via 100R/10n RC filter, heater direct

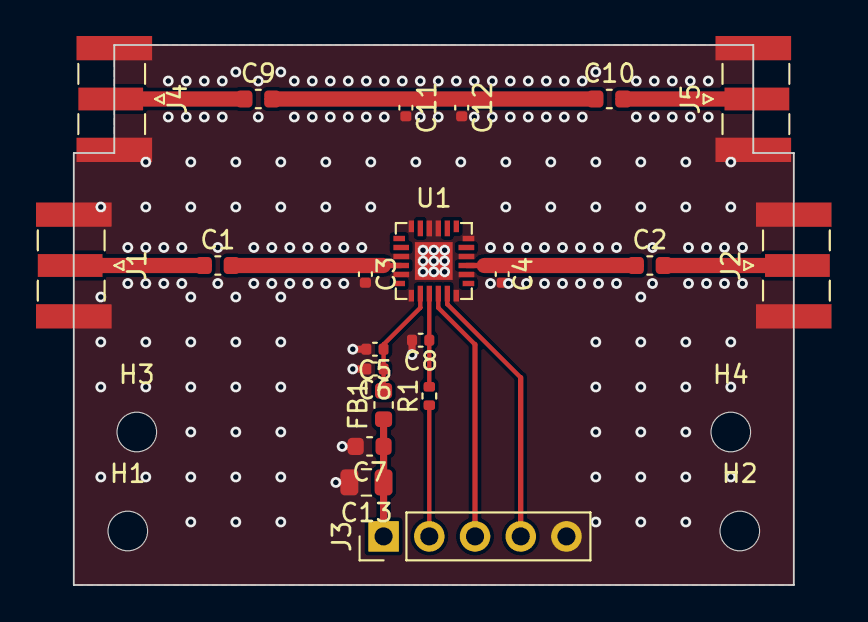
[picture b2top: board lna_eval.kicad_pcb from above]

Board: 2 copper layers, 40.0 x 30.0 mm, 25 parts (0 on the bottom side), 14 nets.

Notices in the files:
readme.md:
GPL-3.0-or-later. OTTER (`thirdparty/otter`) is GPL-3.0-or-later too, see
